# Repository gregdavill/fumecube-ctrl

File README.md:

# fumecube-ctrl

A replacement controller for the Purex Fumecube, a HEPA filter based fume extractor unit.

## What

This controller replaces the existing control board and adds WiFi control using esphome based firmware.
The board runs off a 12V supply, just like the original control board, and features a relay to control the AC to the motor.

Motor enable and control signals are level shifted with mosfets and sent to the motor controller.

The device is intended to be paired with home assistant, so that a wireless switch or my phone/laptop can enable and adjust the speed of the fan.

`docs/fix-speed-controller` contains a kicad schematic of the original 555 based controller for reference. It seems like it was designed to operate off both an AC transformer and the +12V supply found in my unit.

## Why

The original control interface for the fumecube is a potentiometer on the front of the unit, which features a DPST switch that enables AC to the motor controller.
Having to dial the speed all the way done to turn the unit on/off is cumbersome. Additionally, the unit is typically placed under my desk, and leaning down to turn the unit on and off just doesn't happen all the time. 

## Features

Because the fumecube is made with a sheet metal shell, the ESP is designed on a separate PCB and should be fitted outside the unit in a small 3d printed enclosure.

## Assembled boards

## Firmware

The firmware is based on [ESPHome](https://esphome.io) 
ESPHome projects are defined using a yaml config file. The ESPHome tool then pulls in source files to compile the firmware. You can install it and then compile the firmware with the following:

```
pip install esphome
cd src
esphome compile esp-fumecube.yaml
esphome upload esp-fumecube.yaml --device /dev/ttyACM0
```

## Licence

 * Hardware in this repository is licenced under CERN OHL v1.2

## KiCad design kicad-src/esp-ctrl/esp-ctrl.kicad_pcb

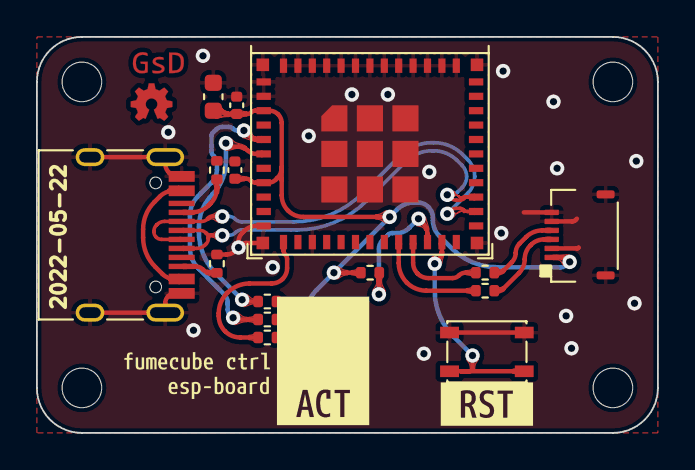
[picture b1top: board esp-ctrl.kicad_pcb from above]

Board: 2 copper layers, 34.5 x 22.0 mm, 24 parts (0 on the bottom side), 18 nets.

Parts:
C1: 10uF; C_0603_1608Metric
C2, C5: 100nF; C_0402_1005Metric
D1: LED_ARGB; 0404LED_RGB
H1, H2, H3, H4: MountingHole_Pad; MountingHole_2.2mm_M2_ISO7380
J1: USB_C_Receptacle_USB2.0; USB_C_Receptacle_HRO_TYPE-C-31-M-12
J3: Conn_01x06_MountingPin; Hirose_FH34SRJ-6S-0.5SH_1x6-1MP_P0.50mm_Horizontal
R1, R2: 5.1k; R_0402_1005Metric
R3: 4.7k; R_0402_1005Metric
R4, R5, R6, R7, R8: 470R; R_0402_1005Metric
SW1: SW_DIP_x01; SW_SPST_PTS810
U1: ESP32-C3-MINI-1
kibuzzard-628A11E7: G***; kibuzzard-628A11E7
kibuzzard-628A126A: G***; kibuzzard-628A126A
kibuzzard-628A1224: G***; kibuzzard-628A1224
kibuzzard-628A1254: G***; kibuzzard-628A1254

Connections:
+3V3: C1.1, C2.1, C5.1, D1.1 (A), J3.1, R3.1, U1.3 (3V3), U1.8 (EN/CHIP_PU)
/dat_N: J1.A7 (D-), J1.B7 (D-), U1.26 (GPIO18/USB_D-)
/dat_P: J1.A6 (D+), J1.B6 (D+), U1.27 (GPIO19/USB_D+)
/enable: J3.3, R7.1
/pwm: J3.4, R4.1
GND: C1.2, C2.2, C5.2, J1.A1 (GND), J1.A12 (GND), J1.B1 (GND), J1.B12 (GND), J1.S1 (SHIELD), J3.2, J3.5, J3.6, J3.MP (MountPin), R1.2, R2.2, SW1.1, U1.1 (GND), U1.2 (GND), U1.11 (GND), U1.14 (GND), U1.36 (GND)
unnamed: D1.2 (RK), R5.1
unnamed: D1.3 (GK), R6.1
unnamed: D1.4 (BK), R8.1
unnamed: J1.A5 (CC1), R2.1
unnamed: J1.B5 (CC2), R1.1
unnamed: R3.2, U1.22 (GPIO8)
unnamed: R4.2, U1.21 (GPIO7)
unnamed: R5.2, U1.12 (GPIO0/ADC1_CH0/XTAL_32K_P)
unnamed: R6.2, U1.6 (GPIO3/ADC1_CH3)
unnamed: R7.2, U1.20 (GPIO6)
unnamed: R8.2, U1.5 (GPIO2/ADC1_CH2)
unnamed: SW1.2, U1.23 (GPIO9)

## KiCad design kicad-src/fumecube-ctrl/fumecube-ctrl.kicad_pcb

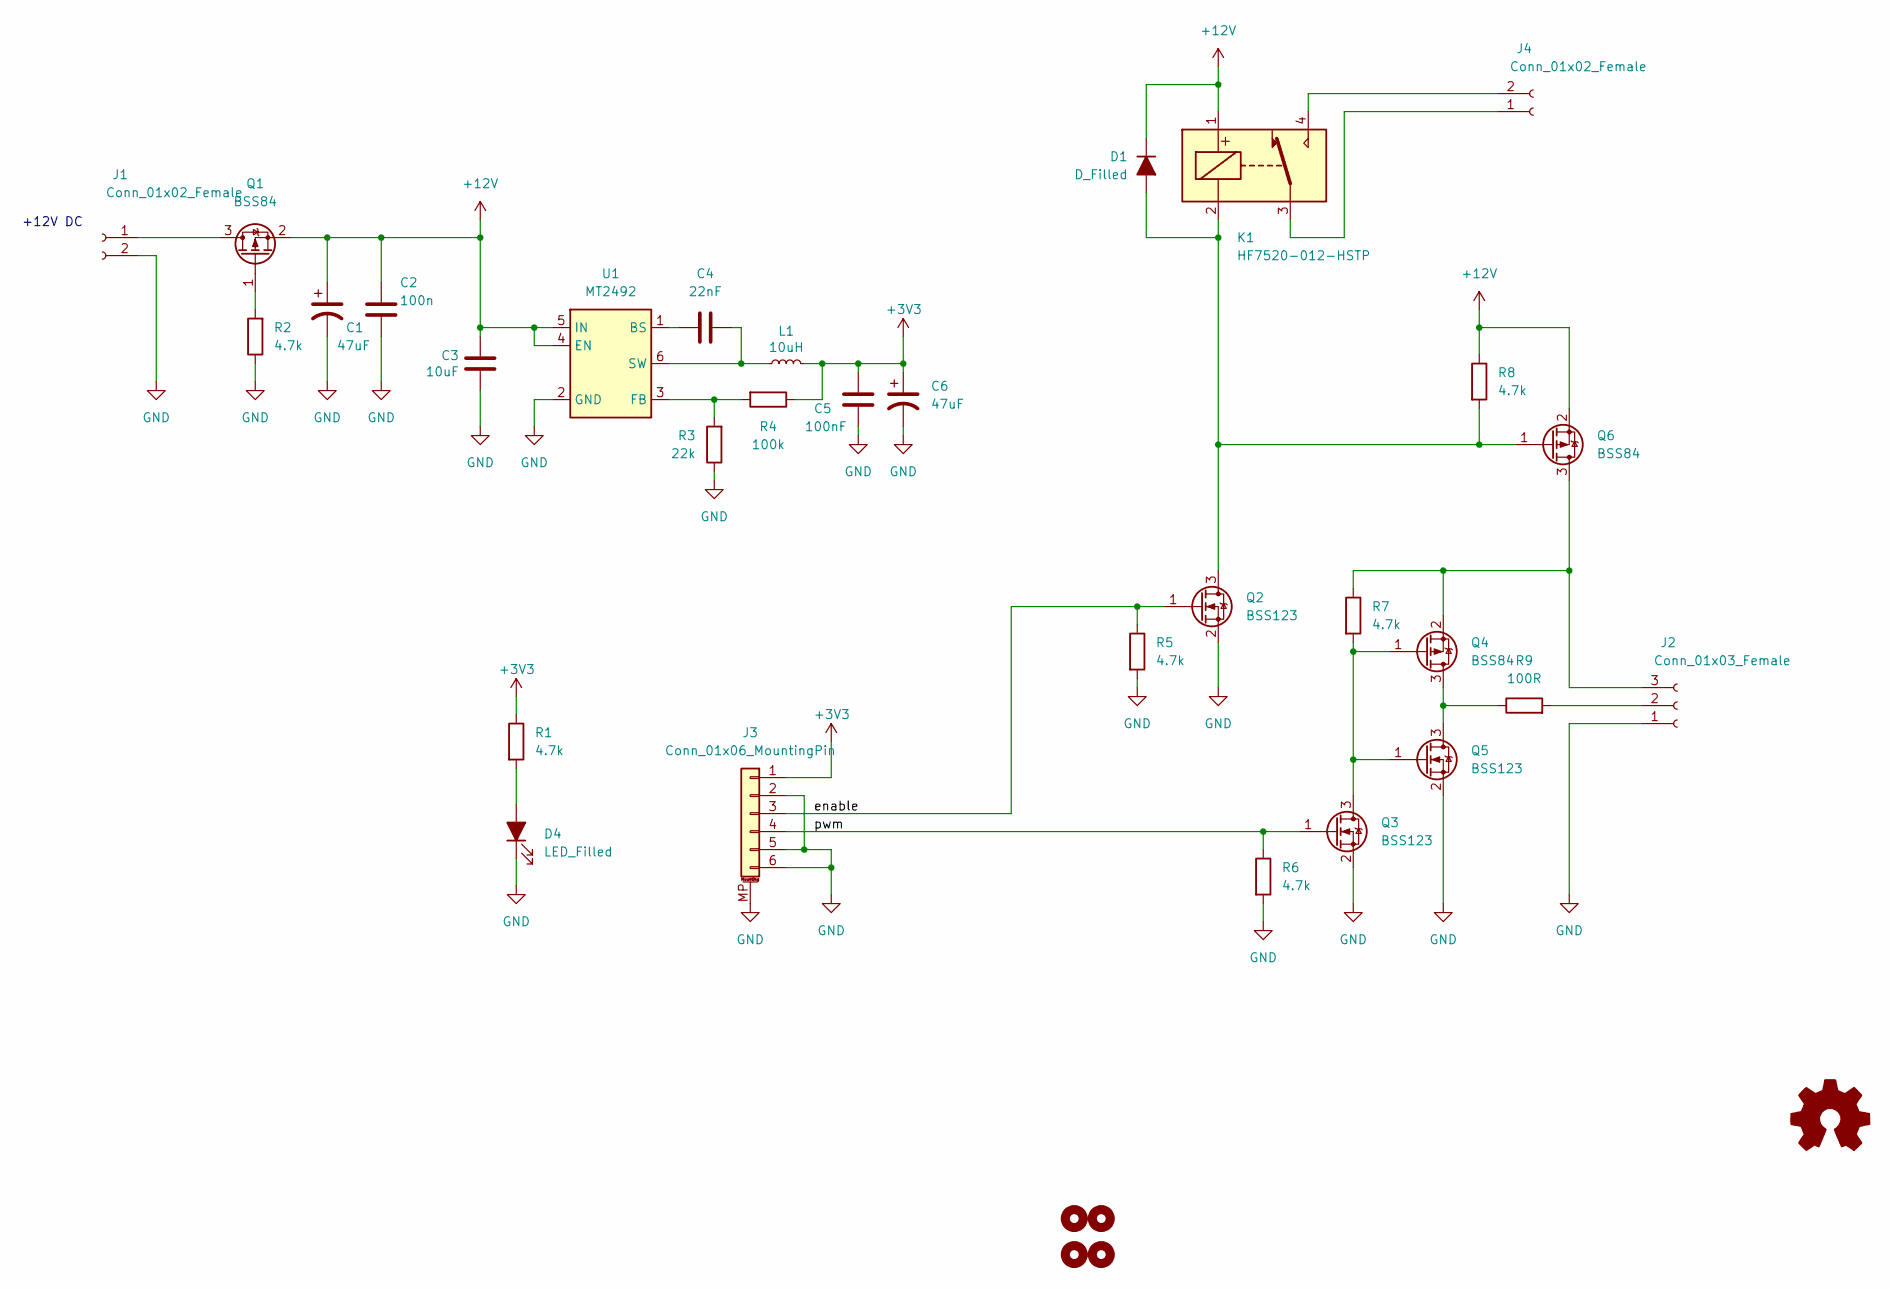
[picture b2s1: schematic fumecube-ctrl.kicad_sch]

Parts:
C1, C6: 47uF; CP_Elec_6.3x4.5; lcsc C72522
C2: 100n; C_0402_1005Metric
C3: 10uF; C_0603_1608Metric
C4: 22nF; C_0402_1005Metric
C5: 100nF; C_0402_1005Metric
D1: D_Filled; D_SOD-523; lcsc C2965561
D4: LED_Filled; LED_0603_1608Metric; lcsc C84269
H1, H2, H3, H4: MountingHole_Pad; MountingHole_4.5mm_Pad
J1, J4: Conn_01x02_Female; TerminalBlock_Phoenix_MKDS-1,5-2_1x02_P5.00mm_Horizontal; lcsc C474881
J2: Conn_01x03_Female; TE_826576-3_1x03_P3.96mm_Vertical; lcsc C2884053
J3: Conn_01x06_MountingPin; Hirose_FH34SRJ-6S-0.5SH_1x6-1MP_P0.50mm_Horizontal
K1: HF7520-012-HSTP; lcsc C53788
L1: 10uH; L_Taiyo-Yuden_NR-30xx; lcsc C340363
Q1, Q4, Q6: BSS84; SOT-23; lcsc C347485
Q2, Q3, Q5: BSS123; SOT-23; lcsc C699301
R1, R2, R5, R6, R7, R8: 4.7k; R_0402_1005Metric
R3: 22k; R_0402_1005Metric
R4: 100k; R_0402_1005Metric
R9: 100R; R_0805_2012Metric
U1: MT2492; SOT-23-6

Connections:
+3V3: C5.1, C6.1, J3.1, L1.2, R1.1, R4.1
+12V: C1.1, C2.1, C3.1, D1.1 (K), K1.1, Q1.2 (S), Q6.2 (S), R8.1, U1.4 (EN), U1.5 (IN)
/enable: J3.3, Q2.1 (G), R5.1
/pwm: J3.4, Q3.1 (G), R6.1
GND: C1.2, C2.2, C3.2, C5.2, C6.2, D4.1 (K), J1.2, J2.1, J3.2, J3.5, J3.6, J3.MP (MountPin), Q2.2 (S), Q3.2 (S), Q5.2 (S), R2.1, R3.1, R5.2, R6.2, U1.2 (GND)
unnamed: C4.1, U1.1 (BS)
unnamed: C4.2, L1.1, U1.6 (SW)
unnamed: D1.2 (A), K1.2, Q2.3 (D), Q6.1 (G), R8.2
unnamed: D4.2 (A), R1.2
unnamed: J1.1, Q1.3 (D)
unnamed: J2.2, R9.2
unnamed: J2.3, Q4.2 (S), Q6.3 (D), R7.1
unnamed: J4.1, K1.3
unnamed: J4.2, K1.4
unnamed: Q1.1 (G), R2.2
unnamed: Q3.3 (D), Q4.1 (G), Q5.1 (G), R7.2
unnamed: Q4.3 (D), Q5.3 (D), R9.1
unnamed: R3.2, R4.2, U1.3 (FB)

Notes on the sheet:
+12V DC

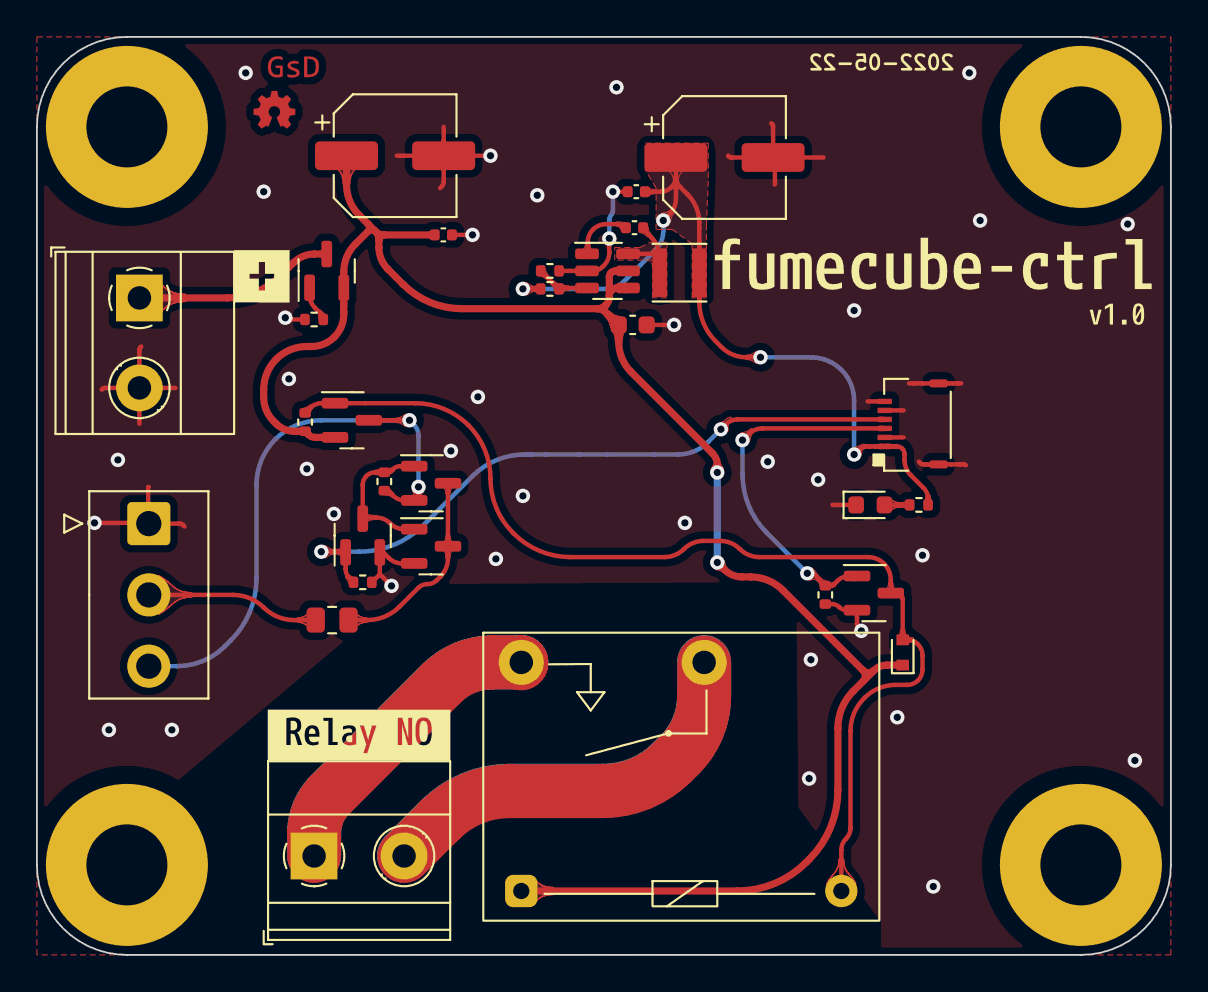
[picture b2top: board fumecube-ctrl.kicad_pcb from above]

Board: 2 copper layers, 63.0 x 51.0 mm, 38 parts (0 on the bottom side), 18 nets.

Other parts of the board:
kibuzzard-6289DEB3: G***; kibuzzard-6289DEB3
kibuzzard-6289EB2D: G***; kibuzzard-6289EB2D
kibuzzard-6289EB16: G***; kibuzzard-6289EB16
kibuzzard-6289EB97: G***; kibuzzard-6289EB97

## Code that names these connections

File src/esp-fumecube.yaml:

esphome:
  name: esp-fumecube
  platformio_options: #https://github.com/esphome/issues/issues/2931
    board_build.flash_mode: dio  

esp32:
  board: esp32-c3-devkitm-1
  framework:
### Arduino
    # type: arduino
    # version: dev
    # platform_version: https://github.com/platformio/platform-espressif32.git#feature/arduino-upstream

### IDF
    type: esp-idf

# Enable logging
logger:
  level: DEBUG

# Enable Home Assistant API
api:

wifi:
  ssid: !secret wifi_ssid
  password: !secret wifi_password
  fast_connect: true

# Enable signal on GPIO6
power_supply:
    id: relay_pwr
    pin: GPIO6

# PWM output on GPIO7
output:
  - platform: ledc
    id: gpio_pwm
    power_supply: relay_pwr
    pin: GPIO7
    #channel: 0
    frequency: 2000Hz

# LED output status out GPIO3
  - platform: gpio
    id: led_green
    pin: GPIO3
    inverted: true
  

# LED status out GPIO2
light:
  - platform: status_led
    id: led_red
    pin: 
      number: GPIO2
      inverted: true

fan:
  - platform: speed
    output: gpio_pwm
    #speed_count: 4
    name: "FumeCube Speed"
    restore_mode: ALWAYS_OFF
    on_turn_on:
      then:
        - output.turn_on: 
            id: led_green
    on_turn_off:
      then:
        - output.turn_off: 
            id: led_green

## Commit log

2022-05-24 Initial commit
    - Add PCB designs
    - Add README
2022-06-10 Update README
    - Add photo of assembled unit
2022-06-10 Add esphome config
2022-06-10 Update esp-ctrl design
2022-06-10 Add CI build
2022-06-10 Fix Typo
2022-06-10 ci: Add example secrets

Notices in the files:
kicad-src/esp-ctrl/esp-ctrl.kicad_pcb:
OSHW: CERN OHL v1.2
